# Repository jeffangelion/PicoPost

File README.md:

# PicoPost

**English** | [Русский](README_ru.md)

**Compact RP2040-based BIOS POST Code Reader & LPC Bus Sniffer**

---

## 📖 About The Project

**PicoPost** is an open-source hardware and firmware solution for capturing and displaying BIOS diagnostic POST codes from PC motherboards over the **LPC (Low Pin Count)** bus.

Built in an ultra-compact form factor (~18.4 × 23.5 mm) around the **Raspberry Pi RP2040** microcontroller (Waveshare RP2040-Zero module or pin-compatible clones).

### Key Features:
- **Hardware LPC Sniffing at 33 MHz:** Utilizes the RP2040 Programmable I/O (PIO) state machine with the system clock overclocked to 198 MHz (33 MHz × 6) to reliably capture LPC I/O port `0x80` write cycles.
- **Dynamic 2-Digit 7-Segment LED Display:** Real-time HEX display of BIOS initialization and error codes. Dynamic multiplexing and PWM brightness control run asynchronously on **Core 1**, ensuring smooth, flicker-free rendering with zero impact on LPC bus capture.
- **Multi-Model Display Support:** Firmware supports popular common-cathode and common-anode dual 7-segment displays (`_2281BY`, `KL2821B`, `E20281I`, `E20281L`).
- **Multi-Vendor Motherboard Header Compatibility:**
  - Standard LPC (2×5 pin, 2.54 mm pitch)
  - ASUS LPC (10-pin TPM / Debug header)
  - Gigabyte LPC (12-pin header)
  - ASUS eLPC (12-pin single-row header)
- **Power State Detection (PWRON):** A dedicated sensing input on GP2 (connected to +3.3V LPC) detects motherboard power transitions (`PON` / `POF`) and automatically blanks the display when power is turned off.
- **Dual Logging (Dual UART / USB Serial):** Streams POST codes to a PC terminal via USB CDC serial (`/dev/ttyACM*`) and over hardware UART (GP0/GP1) for automated test benches and diagnostic logging.
- **3D-Printable Enclosure:** Solid model (`.step`) provided for 3D printing a custom protective snap-fit case (FDM / SLA).
- **Ready-to-Flash Releases (`.uf2`):** Pre-compiled firmware binaries are available on the [GitHub Releases](https://github.com/jeffangelion/PicoPost/releases/latest) page for instant drag-and-drop installation.

---

## 🎥 Demonstration & Testing

<p align="center">
  
  &nbsp;
  
</p>

### Verified Hardware & Motherboards:
- **ASUS ROG Crosshair VIII Dark Hero (AMD AM4 / X570):** Connected via the motherboard TPM / LPC header. Real-time parity verified against the motherboard's onboard 2-digit debug LED.
- **ASUS Desktop Motherboards (Intel / AMD):** Connected via standard 10-pin ASUS TPM header. Full POST sequence captured from cold reset through memory/PCIe initialization up to OS boot handoff.
- **MSI 760GM-P33 (AMD AM3+):** Verified with standard LPC header pinout.

---

## 🖼️ Hardware Design (PCB)

The PCB is designed as a sandwich module: the RP2040-Zero is soldered directly flat onto the castellated pads on the bottom layer, SMD resistors and protection diodes are mounted inside, while the dual 7-segment display and pin headers are placed on the top layer.

<p align="center">
  
  &nbsp;&nbsp;&nbsp;&nbsp;
  
</p>

- Complete KiCad 8 project files: [`hardware/kicad/`](hardware/kicad/).
- Ready-to-order Gerbers ZIP: [`hardware/gerbers/PicoPost_Gerbers.zip`](hardware/gerbers/PicoPost_Gerbers.zip).
- Schematic in PDF: [`hardware/PicoPost_Schematic.pdf`](hardware/PicoPost_Schematic.pdf).
- 3D-printable case model: [`hardware/enclosure/PicoPost_Case.step`](hardware/enclosure/).

---

## 🔌 Pinout & Wiring Guide

### LPC Bus Signals (to RP2040):
- **LPC.AD0** → GP9
- **LPC.AD1** → GP10
- **LPC.AD2** → GP11
- **LPC.AD3** → GP12
- **LPC.CLK** (33 MHz) → GP13
- **LPC.FRAME#** → GP14
- **PWRON** (Power Detect) → GP2 (connect to +3.3V LPC)
- **GND** → Motherboard ground
- **3.3V** → 3.3V power from the LPC header (or via USB Type-C)

> [!TIP]
> Detailed pinout tables for **ASUS 10-pin**, **Gigabyte 12-pin**, and **ASUS eLPC 12-pin** headers are documented in [`docs/pinouts.md`](docs/pinouts.md).

---

## ⚡ Quick Start (Flashing Firmware)

### Method 1: USB Mass Storage (BOOTSEL)
1. Download the latest **`PicoPost.uf2`** from the [GitHub Releases](https://github.com/jeffangelion/PicoPost/releases/latest) page.
2. Hold down the **BOOT** (BOOTSEL) button on the RP2040-Zero module and plug it into your computer via a USB Type-C cable.
3. The board will appear as a removable drive named `RPI-RP2`.
4. Drag and drop `PicoPost.uf2` onto the `RPI-RP2` drive.
5. The device will reboot automatically and start running!

### Method 2: Via `upload.sh` script (picotool)
```bash
cd firmware
./upload.sh
```

---

## 🛠️ Building From Source

### Prerequisites
- CMake (>= 3.17)
- GNU Arm Embedded Toolchain (`arm-none-eabi-gcc`, `arm-none-eabi-g++`)
- Raspberry Pi Pico SDK

### Build Instructions
```bash
# 1. Specify the path to your Pico SDK (if not globally configured):
export PICO_SDK_PATH=/path/to/pico-sdk

# 2. Navigate to the firmware directory and execute the build script:
cd firmware
./build.sh
```
The compiled binary will be placed at `firmware/build/PicoBiosPostCodeReader.uf2`.

---

## ⚙️ Configuration (`Settings.h`)

All pin mappings, 7-segment display models, brightness levels, and baud rates can be configured in [`firmware/src/Settings.h`](firmware/src/Settings.h):

```c
// Select display model:
#define DISPLAY _2281BY
// #define DISPLAY KL2821B
// #define DISPLAY E20281I
// #define DISPLAY E20281L

// Display brightness (0x00 - 0xFF) and segment timing:
#define DISPLAY_BRIGHTNESS  (0xFF / 2)
#define DISPLAY_SEGTIME_US  500

// UART logger baud rate:
#define PUART_BAUDRATE   115200
```

---

## 🧩 Bill of Materials (BOM)

| Ref Des | Component / Value | Package | Qty |
|:---|:---|:---|:---:|
| **U1** | RP2040-Zero (Waveshare or clone) | Castellated SMD | 1 |
| **U2** | 2-Digit 7-Segment Display | 10-pin 15×14 mm / 15×10 mm | 1 |
| **R1–R10** | 36 Ω (33–68 Ω) | SMD 0805 | 10 |
| **D1–D3** | 1N5819WS (Schottky) | SOD-323 | 3 |
| **J2** | Pin Header 1×5 2.54 mm (UART) | THT Vertical | 1 |
| **J3** | Pin Header 2×5 2.54 mm (LPC) | THT Vertical | 1 |

For detailed assembly instructions, see [`docs/bom.md`](docs/bom.md).

---

## 📂 Repository Structure

```
PicoPost/
├── docs/                      # Documentation, pinout tables, BOM and media
│   ├── images/                # Hardware photos, 3D renders, schematics
│   ├── pinouts.md             # Multi-vendor LPC header pinouts
│   └── bom.md                 # Bill of Materials
├── firmware/                  # Firmware source code
│   ├── src/                   # C source files and PIO assembly
│   │   ├── Display/           # Core 1 dynamic 7-segment display driver
│   │   ├── LPCPwrDet/         # LPC PWRON power state monitor
│   │   ├── LPCSniffer/        # PIO-based LPC bus sniffer
│   │   ├── lpc_bus_sniffer.pio# PIO assembly program for LPC frames
│   │   ├── Main.c             # Main entry point & multicore launcher
│   │   └── Settings.h         # Hardware pins, clock, and display configuration
│   ├── CMakeLists.txt         # CMake build configuration
│   └── build.sh / upload.sh   # Build and flash automation scripts
├── hardware/                  # Hardware design files (KiCad 8)
│   ├── kicad/                 # KiCad schematics, PCB layout, footprints
│   ├── gerbers/               # Gerber & drill files, ready-to-order ZIP
│   ├── enclosure/             # 3D-printable case model (STEP)
│   └── PicoPost_Schematic.pdf # PDF schematic export
├── LICENSE                    # Apache License 2.0
├── NOTICE                     # Copyright notices
├── README.md                  # Main documentation (English)
└── README_ru.md               # Документация (Русский)
```

---

## 📜 License & Credits

- This project is distributed under the **Apache License 2.0**. See [LICENSE](LICENSE) and [NOTICE](NOTICE) for details.
- Original hardware design (schematics, PCB), firmware modular architecture, and 7-segment display driver authored by **🦊**. Repository prepared, maintained, and published by [jeffangelion](https://github.com/jeffangelion).
- LPC bus sniffer algorithm based on [RasPiPicoSDK-PicoBiosPostCodeReader](https://github.com/MrGreensWorkshop/RasPiPicoSDK-PicoBiosPostCodeReader) by **Mr. Green's Workshop** ([https://www.MrGreensWorkshop.com](https://www.MrGreensWorkshop.com)).

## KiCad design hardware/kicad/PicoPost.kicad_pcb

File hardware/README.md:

# PicoPost Hardware

This folder contains all KiCad design files, schematics, fabrication gerbers, and documentation for the PicoPost PCB.

## Files & Directories

- `kicad/`: Complete KiCad 7 / 8 project:
  - `PicoPost.kicad_pro` — Project file
  - `PicoPost.kicad_sch` — Root schematic sheet
  - `PicoPost.kicad_pcb` — Board layout
  - `7S2D.kicad_sch` — 7-Segment display subsystem
  - `SoM.kicad_sch` — RP2040-Zero controller subsystem
  - `LPC.kicad_sch` — LPC header connector
  - `UART.kicad_sch` — UART header
  - `LPC_ASUS_10Pin.kicad_sch`, `LPC_GIGABYTE_12Pin.kicad_sch`, `eLPC_ASUS_12Pin.kicad_sch` — Vendor-specific LPC breakouts
  - `Library.kicad_sym`, `Library.pretty/` — Project footprints and symbols
  - `PinHeader_2x05_P2.54mm_Vertical.step` — 3D model
- `gerbers/`:
  - `PicoPost_Gerbers.zip` — Ready to upload to JLCPCB, PCBWay, etc.
  - Extracted `.gbr` and `.drl` files.
- `enclosure/`:
  - `PicoPost_Case.step` — 3D printable protective enclosure model.
- `PicoPost_Schematic.pdf` — Complete multi-page schematic in PDF format.

## PCB Specs
- **Dimensions**: ~18.4 mm × 23.5 mm (ultra-compact)
- **Layers**: 2 Layers (FR-4, 1.6mm or 1.0mm thickness recommended)
- **Finish**: HASL lead-free or ENIG (recommended for castellated soldering)
- **Solder Mask**: Black, Green, Purple, etc.

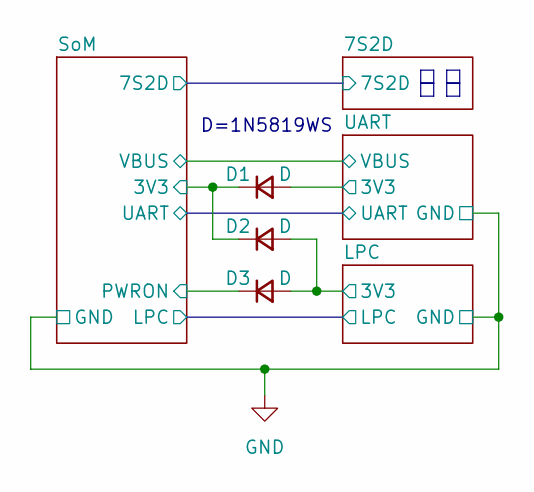
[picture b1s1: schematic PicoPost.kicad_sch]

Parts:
D1, D2, D3: D; D_SOD-323

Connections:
/LPC/3V3: D2.2 (A), D3.2 (A); also elsewhere on the board
/SoM/3V3: D1.1 (K), D2.1 (K); also elsewhere on the board
/SoM/PWRON: D3.1 (K); also elsewhere on the board
/UART/3V3: D1.2 (A); also elsewhere on the board

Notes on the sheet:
D=1N5819WS

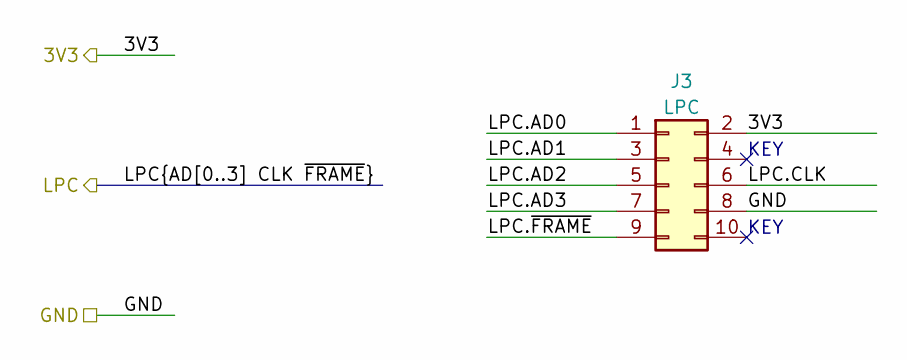
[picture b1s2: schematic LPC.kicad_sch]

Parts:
J3: LPC; PinHeader_2x05_P2.54mm_Vertical

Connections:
/LPC/3V3: J3.2; also elsewhere on the board
/LPC/LPC.AD0: J3.1; also elsewhere on the board
/LPC/LPC.AD1: J3.3; also elsewhere on the board
/LPC/LPC.AD2: J3.5; also elsewhere on the board
/LPC/LPC.AD3: J3.7; also elsewhere on the board
/LPC/LPC.CLK: J3.6; also elsewhere on the board
/LPC/LPC.~FRAME: J3.9; also elsewhere on the board
GND: J3.8; also elsewhere on the board

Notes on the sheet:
KEY

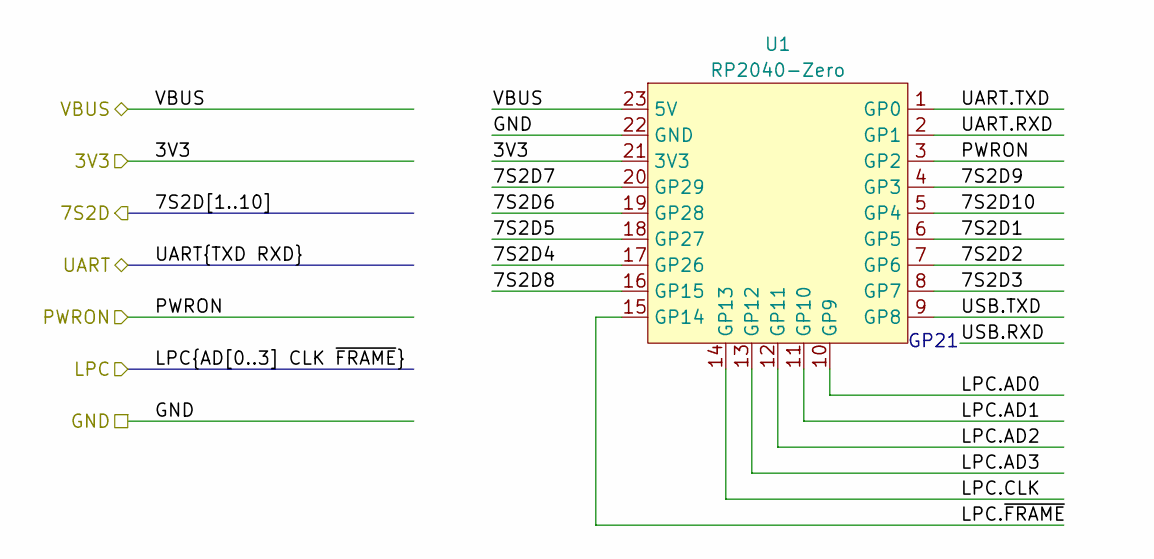
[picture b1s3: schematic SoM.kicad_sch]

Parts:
U1: RP2040-Zero; RP2040-Zero TNT

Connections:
/7S2D/7S2D1: U1.6 (GP5); also elsewhere on the board
/7S2D/7S2D2: U1.7 (GP6); also elsewhere on the board
/7S2D/7S2D3: U1.8 (GP7); also elsewhere on the board
/7S2D/7S2D4: U1.17 (GP26); also elsewhere on the board
/7S2D/7S2D5: U1.18 (GP27); also elsewhere on the board
/7S2D/7S2D6: U1.19 (GP28); also elsewhere on the board
/7S2D/7S2D7: U1.20 (GP29); also elsewhere on the board
/7S2D/7S2D8: U1.16 (GP15); also elsewhere on the board
/7S2D/7S2D9: U1.4 (GP3); also elsewhere on the board
/7S2D/7S2D10: U1.5 (GP4); also elsewhere on the board
/LPC/LPC.AD0: U1.10 (GP9); also elsewhere on the board
/LPC/LPC.AD1: U1.11 (GP10); also elsewhere on the board
/LPC/LPC.AD2: U1.12 (GP11); also elsewhere on the board
/LPC/LPC.AD3: U1.13 (GP12); also elsewhere on the board
/LPC/LPC.CLK: U1.14 (GP13); also elsewhere on the board
/LPC/LPC.~FRAME: U1.15 (GP14); also elsewhere on the board
/SoM/3V3: U1.21 (3V3); also elsewhere on the board
/SoM/PWRON: U1.3 (GP2); also elsewhere on the board
/SoM/UART.RXD: U1.2 (GP1); also elsewhere on the board
/SoM/UART.TXD: U1.1 (GP0); also elsewhere on the board
/SoM/VBUS: U1.23 (5V); also elsewhere on the board
GND: U1.22 (GND); also elsewhere on the board

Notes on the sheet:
GP21

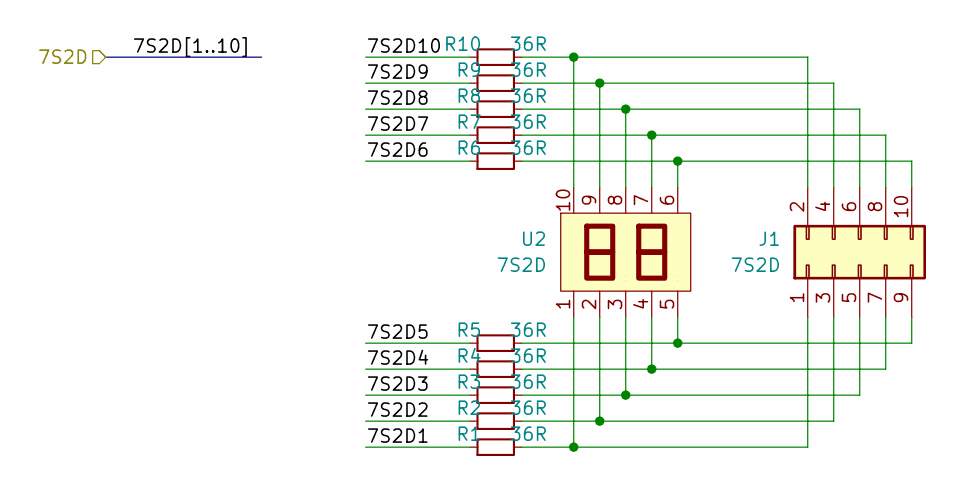
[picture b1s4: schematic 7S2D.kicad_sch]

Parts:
J1: 7S2D; PinHeader_2x05_P2.54mm_Vertical_SMD
R1, R2, R3, R4, R5, R6, R7, R8, R9, R10: 36R; R_0805_2012Metric
U2: 7S2D; Display_7S2D_10Pin_150x100

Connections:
/7S2D/7S2D1: R1.1; also elsewhere on the board
/7S2D/7S2D2: R2.1; also elsewhere on the board
/7S2D/7S2D3: R3.1; also elsewhere on the board
/7S2D/7S2D4: R4.1; also elsewhere on the board
/7S2D/7S2D5: R5.1; also elsewhere on the board
/7S2D/7S2D6: R6.1; also elsewhere on the board
/7S2D/7S2D7: R7.1; also elsewhere on the board
/7S2D/7S2D8: R8.1; also elsewhere on the board
/7S2D/7S2D9: R9.1; also elsewhere on the board
/7S2D/7S2D10: R10.1; also elsewhere on the board
unnamed: J1.1, R1.2, U2.1
unnamed: J1.2, R10.2, U2.10
unnamed: J1.3, R2.2, U2.2
unnamed: J1.4, R9.2, U2.9
unnamed: J1.5, R3.2, U2.3
unnamed: J1.6, R8.2, U2.8
unnamed: J1.7, R4.2, U2.4
unnamed: J1.8, R7.2, U2.7
unnamed: J1.9, R5.2, U2.5
unnamed: J1.10, R6.2, U2.6

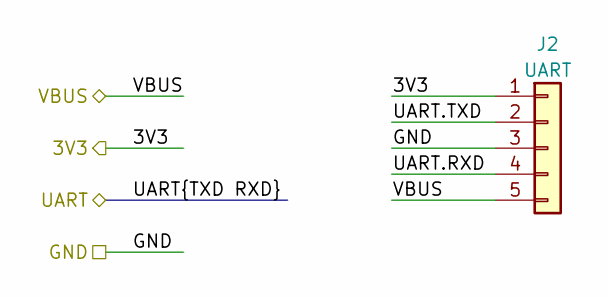
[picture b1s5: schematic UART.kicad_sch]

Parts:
J2: UART; PinHeader_1x05_P2.54mm_Vertical

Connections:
/SoM/UART.RXD: J2.4; also elsewhere on the board
/SoM/UART.TXD: J2.2; also elsewhere on the board
/SoM/VBUS: J2.5; also elsewhere on the board
/UART/3V3: J2.1; also elsewhere on the board
GND: J2.3; also elsewhere on the board

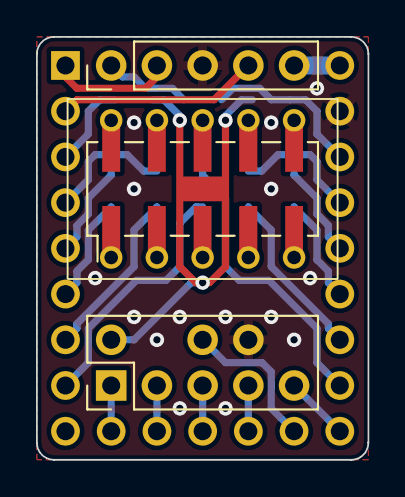
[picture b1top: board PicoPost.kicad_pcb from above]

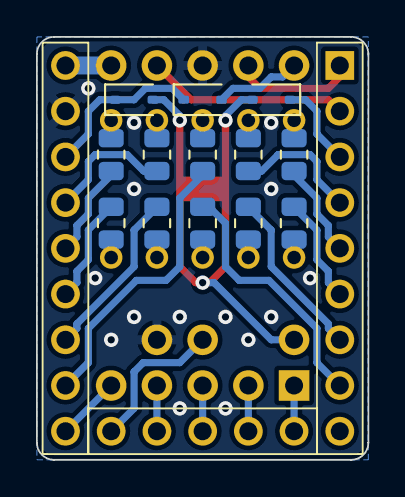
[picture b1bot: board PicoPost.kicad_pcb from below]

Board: 2 copper layers, 18.4 x 23.5 mm, 18 parts (14 on the bottom side), 34 nets.

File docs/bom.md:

# PicoPost Bill of Materials (BOM)

| Ref Des | Component / Value | Package / Footprint | Qty | Description / Recommendation |
|:---|:---|:---|:---:|:---|
| **U1** | RP2040-Zero | SMD Castellated Module | 1 | Waveshare RP2040-Zero or pin-compatible clone |
| **U2** | 2-Digit 7-Segment Display | 10-Pin 15x14mm or 15x10mm | 1 | Models: 2281BY, KL2821B, E20281I, E20281L (Common Cathode or Anode) |
| **R1–R10** | 36 Ω (or 33 Ω – 68 Ω) | 0805 SMD | 10 | Current-limiting resistors for 7-segment display segments |
| **D1–D3** | 1N5819WS (or BAT54, SS14) | SOD-323 SMD | 3 | Schottky barrier diodes for power multiplexing / reverse protection |
| **J1** | 2x5 Pin Header (Optional) | 2.54mm SMD / THT | 1 | Optional header for external 7-segment display module |
| **J2** | 1x5 Pin Header | 2.54mm Vertical THT | 1 | UART header for debug logging |
| **J3** | 2x5 Pin Header | 2.54mm Vertical THT | 1 | Standard LPC bus connector |

### Assembly Notes
1. **Diodes**: Ensure correct polarity orientation of SOD-323 cathode stripes (matches schematic `K` pin).
2. **Resistors**: Standard 0805 SMD resistors, 36 Ω recommended for bright crisp segments at 3.3V logic, but 33 Ω to 68 Ω also work well.
3. **RP2040-Zero**: Solder using castellated edge pads. The board is designed so the module sits flat.
4. **Enclosure**: Can be 3D printed (FDM or SLA) to protect the module during diagnostics.

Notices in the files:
README.md:
License: Apache 2.0
